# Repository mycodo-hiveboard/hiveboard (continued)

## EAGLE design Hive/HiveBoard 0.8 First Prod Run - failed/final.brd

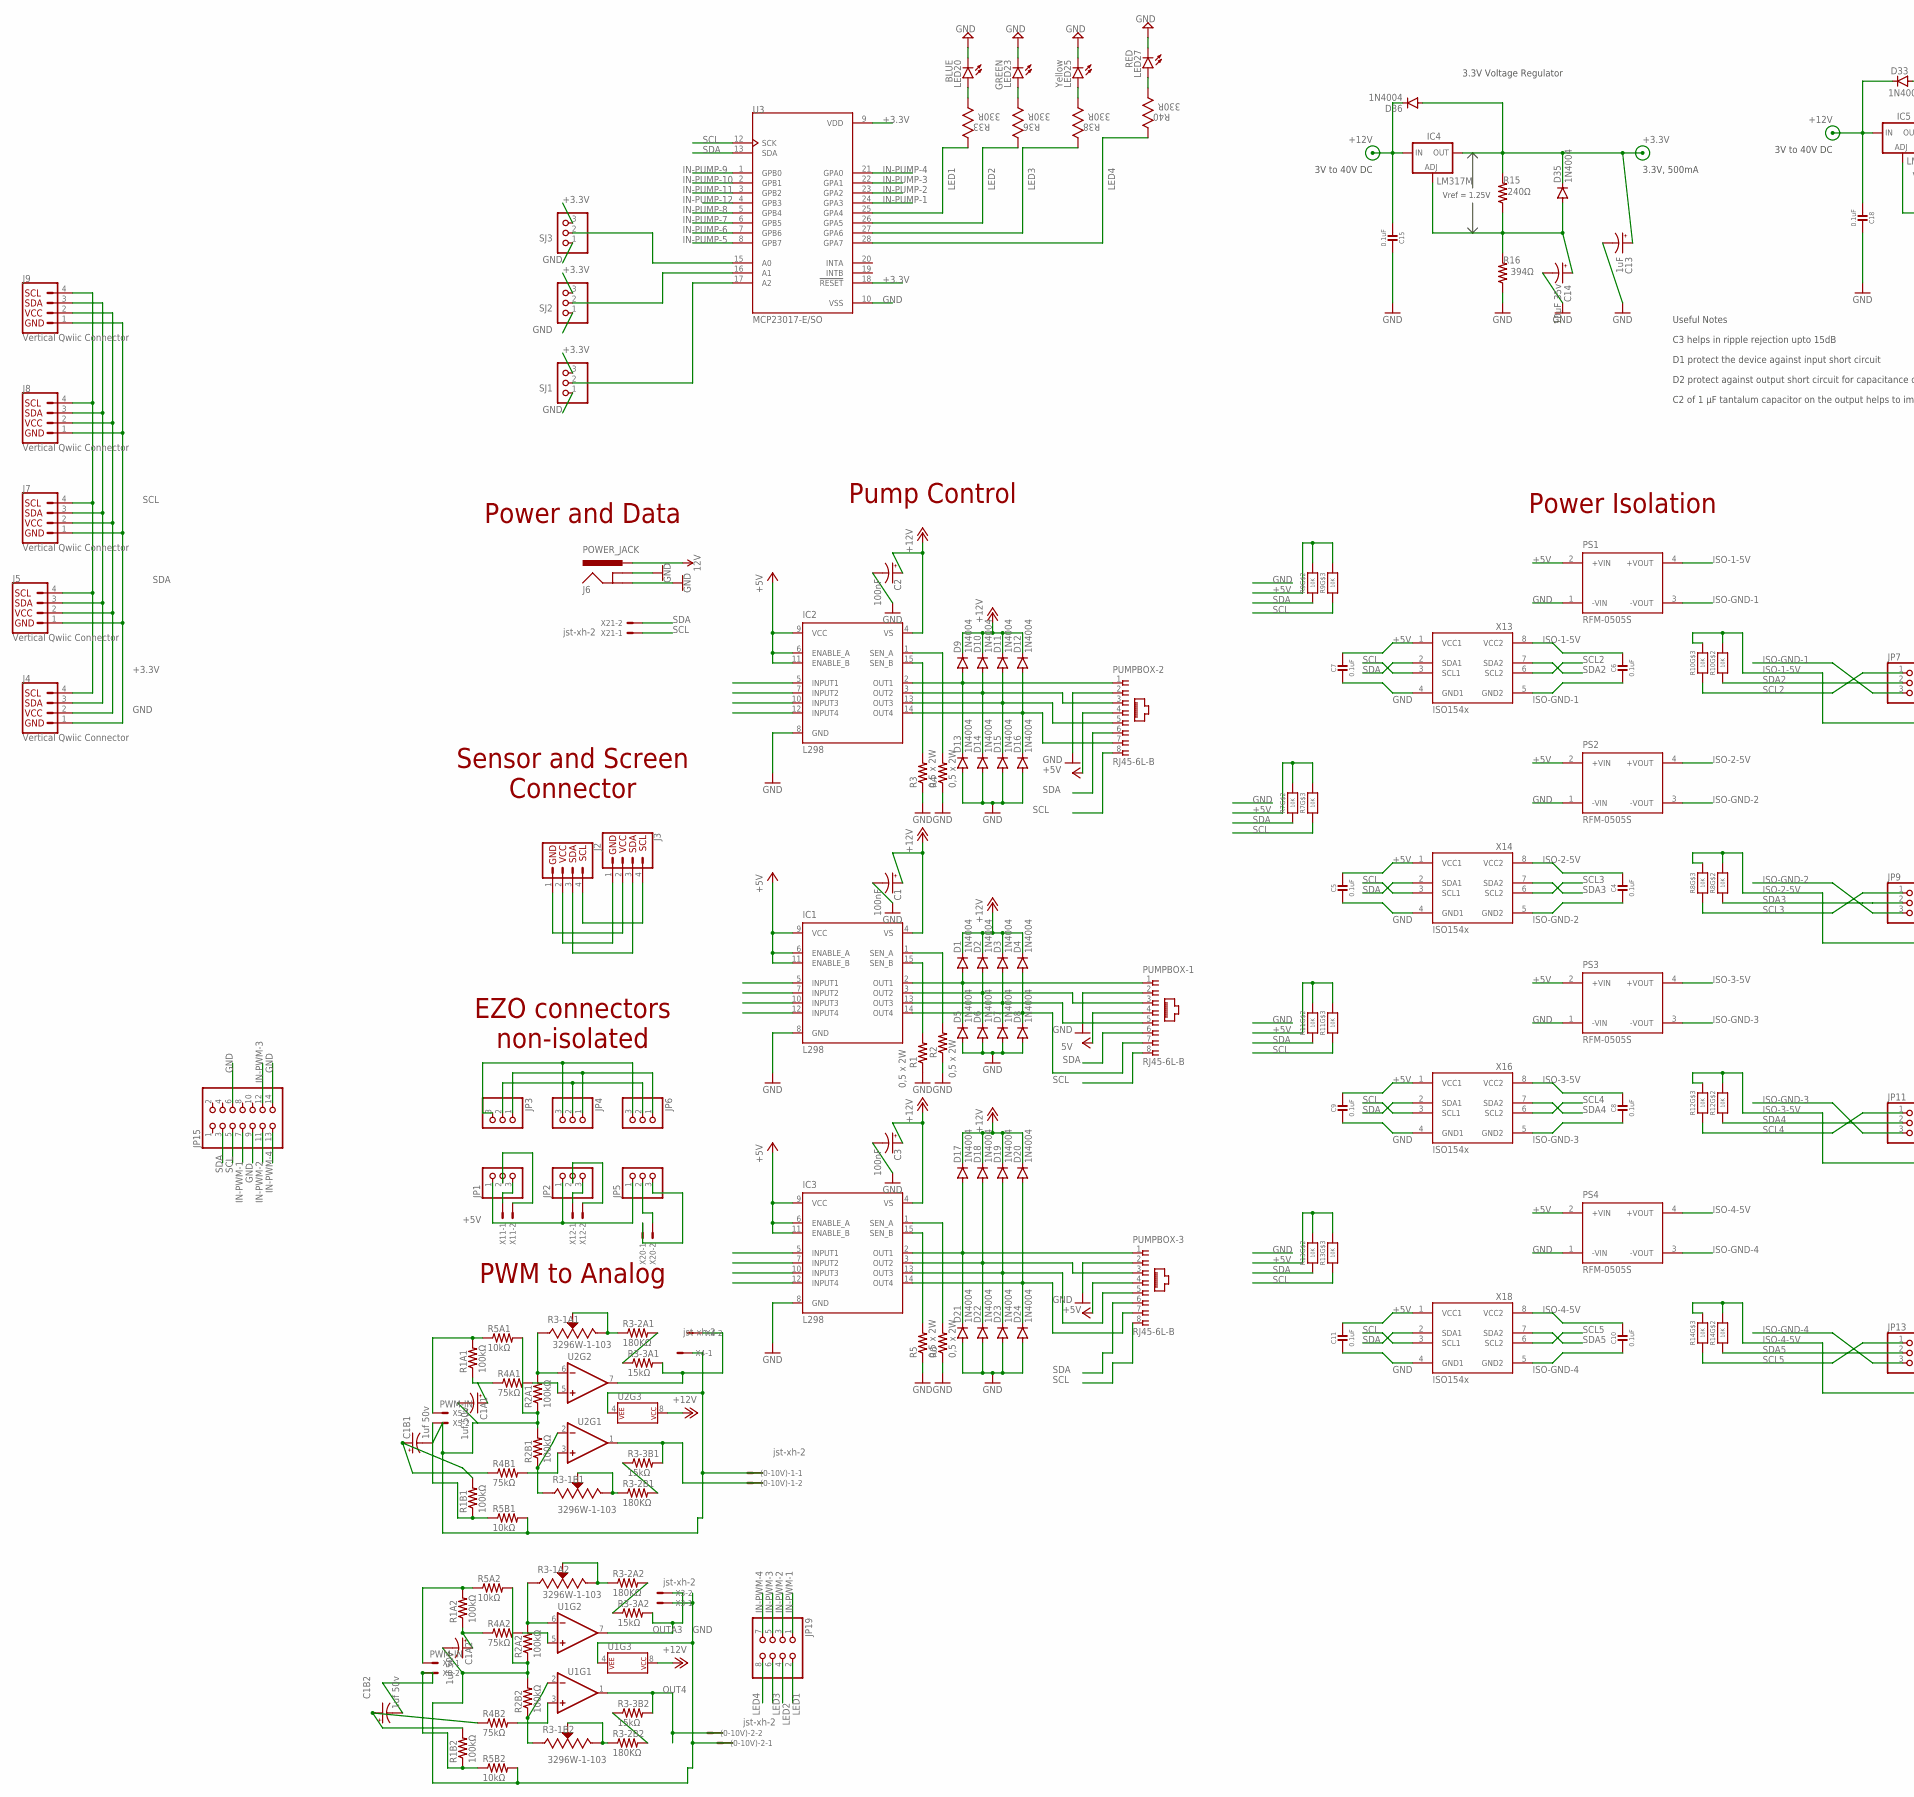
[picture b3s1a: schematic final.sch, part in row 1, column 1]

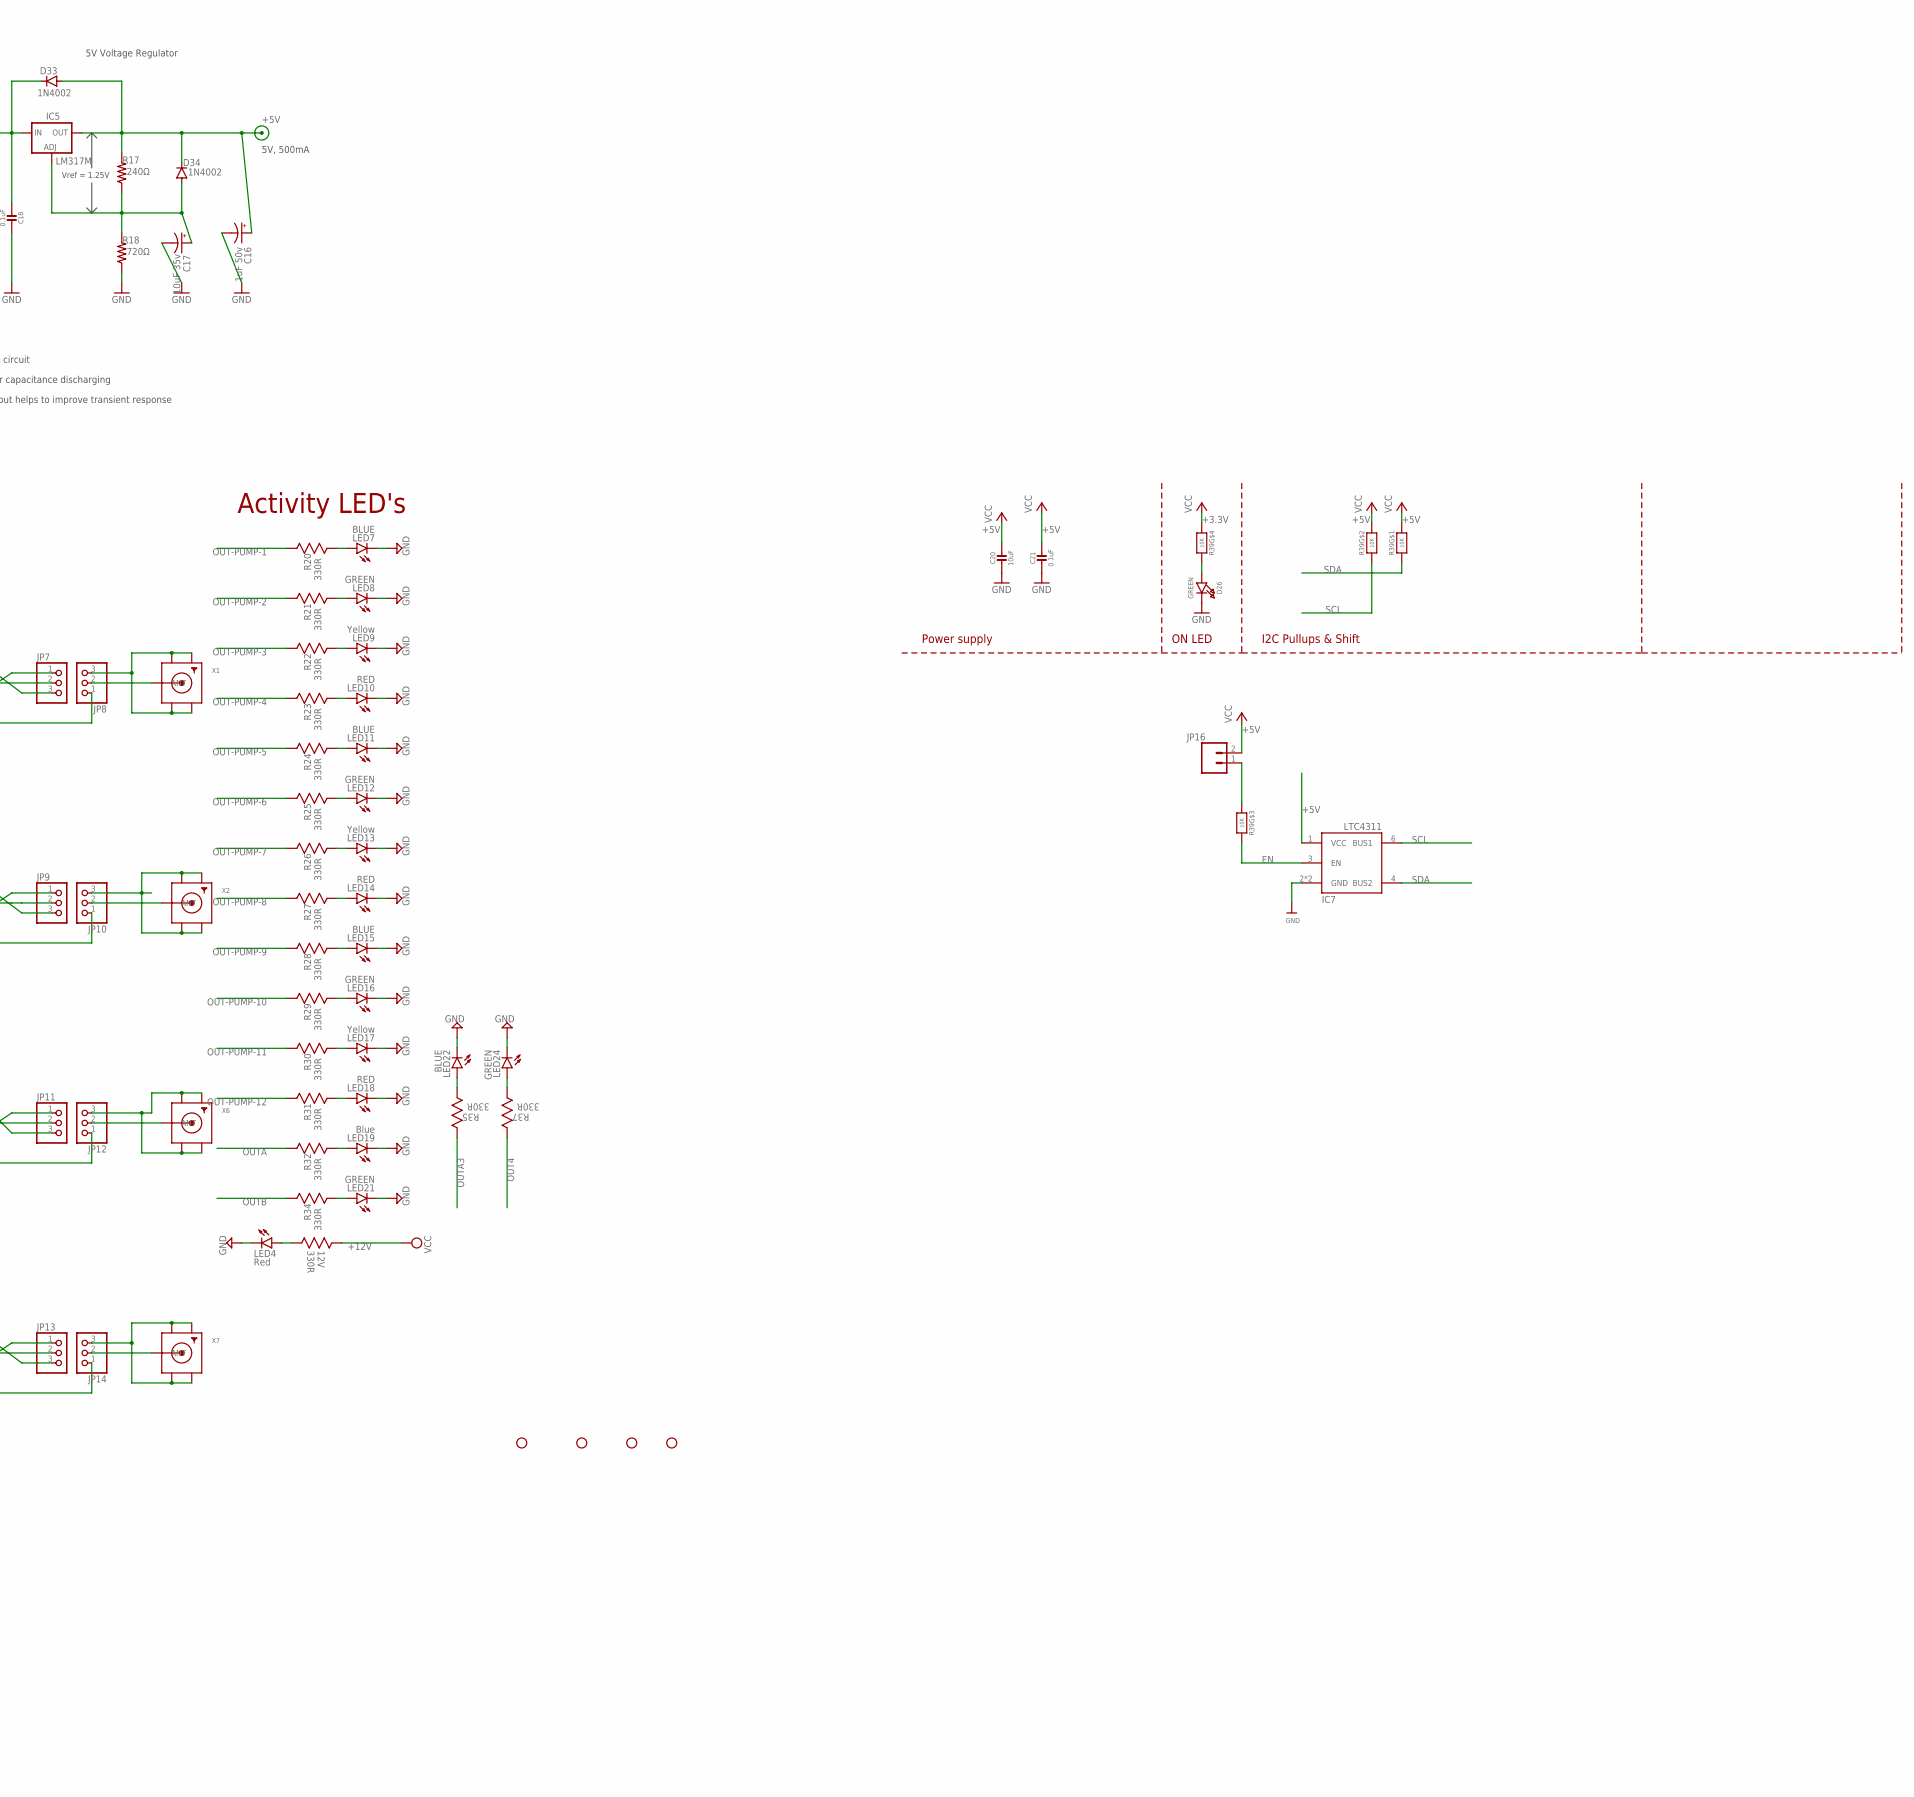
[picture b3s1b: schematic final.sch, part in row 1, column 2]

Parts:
12V: 330R; RESC1608X60N
(0-10V)-1, (0-10V)-2: jst-xh-2; JST-XH-02-PACKAGE-LONG-PAD
C1, C2, C3: 100nF; UD-4X5,8_NICHICON
C1A1, C1A2, C1B1, C1B2: 1uf 50v; UD-4X5,8_NICHICON
C4, C5, C6, C7, C8, C9, C10, C11, C15, C18, C21: 0.1uF; 0603-NO
C13: 1uF; UD-4X5,8_NICHICON
C14, C17: 10uF 35v; UD-4X5,8_NICHICON
C16: 1uF 50v; UD-4X5,8_NICHICON
C20: 10uF; 0805-NO
D1, D2, D3, D4, D5, D6, D7, D8, D9, D10, D11, D12, D13, D14, D15, D16, D17, D18, D19, D20, D21, D22, D23, D24, D35, D36: 1N4004; DO214BA
D26: GREEN; CHIPLED_0603_NOOUTLINE
D33, D34: 1N4002; DO214BA
H5, H6, H7, H8: STAND-OFF
IC1, IC2, IC3: L298; MULTIWATT-15
IC4, IC5: LM317MBSTT3; SOT223; PARTNUMBER LM317M
IC7: LTC4311_SC70; SC70-6L
J2, J3: I2C_STANDARD; 1X04
J4, J5, J7, J8, J9: Vertical Qwiic Connector; JST04_1MM_VERT
J6: POWER_JACK; POWER_JACK_PTH
JP1, JP2, JP3, JP4, JP5, JP6, JP7, JP8, JP9, JP10, JP11, JP12, JP13, JP14: PINHD-1X3CB; 1X03-CLEANBIG
JP15: PINHD-2X7; 2X07
JP16: CONN_02; 1X02
JP19: PINHD-2X4; 2X04
LED4: Red; LED-0603
LED7, LED11, LED15, LED20, LED22: BLUE; LED-0603
LED8, LED12, LED16, LED21, LED23, LED24: GREEN; LED-0603
LED9, LED13, LED17, LED25: Yellow; LED-0603
LED10, LED14, LED18, LED27: RED; LED-0603
LED19: Blue; LED-0603
PS1, PS2, PS3, PS4: RFM-0505S; CONV_RFM-0505S
PUMPBOX-1, PUMPBOX-2, PUMPBOX-3: RJ45-6L-B; RJ45-NO-SHIELD
R1, R2, R3, R4, R5, R6: 0,5 x 2W; R2512
R1A1, R1A2, R1B1, R1B2, R2A1, R2A2, R2B1, R2B2: 100kΩ; M1206
R3-1A1, R3-1A2, R3-1B1, R3-1B2: 3296W-1-103; TRIM_3296W-1-103
R3-2A1, R3-2A2, R3-2B1, R3-2B2: 180KΩ; M1206
R3-3A1, R3-3A2, R3-3B1, R3-3B2: 15kΩ; M1206
R4A1, R4A2, R4B1, R4B2: 75kΩ; M1206
R5A1, R5A2, R5B1, R5B2: 10kΩ; M1206
R7, R8, R9, R10, R11, R12, R13, R14, R39: 10K; RESPACK_4X0603
R15, R17: 240Ω; M0805
R16: 394Ω; M0805
R18: 720Ω; M0805
R20, R21, R22, R23, R24, R25, R26, R27, R28, R29, R30, R31, R32, R33, R34, R35, R36, R37, R38, R40: 330R; RESC1608X60N
SJ1, SJ2, SJ3: PINHD-1X3; 1X03
U1, U2: LM358; SO08
U3: MCP23017-E/SO; SOIC127P1030X265-28N
X1, X2, X6, X7: SMACONNECTOR_EDGE; SMA_EDGELAUNCH
X3, X4, X11, X12, X20, X21: jst-xh-2; JST-XH-02-PACKAGE-LONG-PAD
X5, X8: PWM-IN; JST-XH-02-PACKAGE-LONG-PAD
X13, X14, X16, X18: ISO154X; SOIC8_150MIL

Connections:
12V: J6.PWR
+3.3V: C13.+, D35.C, D36.A, IC4.4 (OUT), J4.2, J5.2, J7.2, J8.2, J9.2, R15.2, R39.4 (1), SJ1.3, SJ2.3, SJ3.3, U3.9 (VDD), U3.18 (!RESET)
+5V: C5.1, C7.1, C9.1, C11.1, C16.+, C20.1, C21.1, D33.A, D34.C, IC1.6 (ENABLE_A), IC1.9 (VCC), IC1.11 (ENABLE_B), IC2.6 (ENABLE_A), IC2.9 (VCC), IC2.11 (ENABLE_B), IC3.6 (ENABLE_A), IC3.9 (VCC), IC3.11 (ENABLE_B), IC5.4 (OUT), IC7.1 (VCC), J2.1, J3.2, JP1.1, JP2.1, JP5.1, JP16.2, PS1.2 (+VIN), PS2.2 (+VIN), PS3.2 (+VIN), PS4.2 (+VIN), PUMPBOX-1.4, PUMPBOX-2.4, PUMPBOX-3.4, R7.6 (2), R7.7 (2), R9.6 (2), R9.7 (2), R11.6 (2), R11.7 (2), R13.6 (2), R13.7 (2), R17.2, R39.7 (2), R39.8 (2), X13.1 (VCC1), X14.1 (VCC1), X16.1 (VCC1), X18.1 (VCC1)
+12V: 12V.1 (R1), C1.+, C2.+, C3.+, C15.2, C18.2, D1.C, D2.C, D3.C, D4.C, D9.C, D10.C, D11.C, D12.C, D17.C, D18.C, D19.C, D20.C, D33.C, D36.C, IC1.4 (VS), IC2.4 (VS), IC3.4 (VS), IC4.3 (IN), IC5.3 (IN), U1.8 (P$V+), U2.8 (P$V+)
EN: IC7.3 (EN), R39.6 (2)
GND: (0-10V)-1.1, (0-10V)-2.1, C1.-, C1A1.-, C1A2.-, C1B1.-, C2.-, C3.-, C5.2, C7.2, C9.2, C11.2, C13.-, C14.-, C15.1, C16.-, C17.-, C18.1, C20.2, C21.2, D5.A, D6.A, D7.A, D8.A, D13.A, D14.A, D15.A, D16.A, D21.A, D22.A, D23.A, D24.A, D26.C, IC1.8 (GND), IC2.8 (GND), IC3.8 (GND), IC7.2 (GND), IC7.5 (GND), J2.2, J3.1, J4.1, J5.1, J6.GND, J6.GNDBREAK, J7.1, J8.1, J9.1, JP3.3, JP4.3, JP6.3, JP15.6, JP15.9, JP15.14, LED4.C, LED7.C, LED8.C, LED9.C, LED10.C, LED11.C, LED12.C, LED13.C, LED14.C, LED15.C, LED16.C, LED17.C, LED18.C, LED19.C, LED20.C, LED21.C, LED22.C, LED23.C, LED24.C, LED25.C, LED27.C, PS1.1 (-VIN), PS2.1 (-VIN), PS3.1 (-VIN), PS4.1 (-VIN), PUMPBOX-1.2, PUMPBOX-2.2, PUMPBOX-3.2, R1.1, R2.1, R2A1.1, R2A2.1, R2B1.2, R2B2.2, R3.1, R4.1, R5.1, R5A1.2, R5A2.2, R5B1.2, R5B2.2, R6.1, R16.1, R18.1, SJ1.1, SJ2.1, SJ3.1, U1.4 (P$V-), U2.4 (P$V-), U3.10 (VSS), X3.1, X4.1, X13.4 (GND1), X14.4 (GND1), X16.4 (GND1), X18.4 (GND1)
IN-PUMP-1: IC1.5 (INPUT1), U3.24 (GPA3)
IN-PUMP-2: IC1.7 (INPUT2), U3.23 (GPA2)
IN-PUMP-3: IC1.10 (INPUT3), U3.22 (GPA1)
IN-PUMP-4: IC1.12 (INPUT4), U3.21 (GPA0)
IN-PUMP-5: IC2.5 (INPUT1), U3.8 (GPB7)
IN-PUMP-6: IC2.7 (INPUT2), U3.7 (GPB6)
IN-PUMP-7: IC2.10 (INPUT3), U3.6 (GPB5)
IN-PUMP-8: IC2.12 (INPUT4), U3.5 (GPB4)
IN-PUMP-9: IC3.5 (INPUT1), U3.1 (GPB0)
IN-PUMP-10: IC3.7 (INPUT2), U3.2 (GPB1)
IN-PUMP-11: IC3.10 (INPUT3), U3.3 (GPB2)
IN-PUMP-12: IC3.12 (INPUT4), U3.4 (GPB3)
IN-PWM-1: JP15.7, JP19.1, R1A1.2, R5A1.1, X5.1
IN-PWM-2: JP15.11, JP19.3, R1B1.1, R5B1.1, X5.2
IN-PWM-3: JP15.12, JP19.5, R1A2.2, R5A2.1, X8.1
IN-PWM-4: C1B2.-, JP15.13, JP19.7, R1B2.1, R5B2.1, X8.2
ISO-1-5V: C6.1, JP8.1, PS1.4 (+VOUT), R10.6 (2), R10.7 (2), X13.8 (VCC2)
ISO-2-5V: C4.1, JP10.1, PS2.4 (+VOUT), R8.6 (2), R8.7 (2), X14.8 (VCC2)
ISO-3-5V: C8.1, JP12.1, PS3.4 (+VOUT), R12.6 (2), R12.7 (2), X16.8 (VCC2)
ISO-4-5V: C10.1, JP14.1, PS4.4 (+VOUT), R14.6 (2), R14.7 (2), X18.8 (VCC2)
ISO-GND-1: C6.2, JP7.3, PS1.3 (-VOUT), X13.5 (GND2)
ISO-GND-2: C4.2, JP9.3, PS2.3 (-VOUT), X14.5 (GND2)
ISO-GND-3: C8.2, JP11.3, PS3.3 (-VOUT), X16.5 (GND2)
ISO-GND-4: C10.2, JP13.3, PS4.3 (-VOUT), X18.5 (GND2)
LED1: JP19.2, R33.1 (R1), U3.25 (GPA4)
LED2: JP19.4, R36.1 (R1), U3.26 (GPA5)
LED3: JP19.6, R38.1 (R1), U3.27 (GPA6)
LED4: JP19.8, R40.1 (R1), U3.28 (GPA7)
unnamed: IC2.1 (SEN_A), R4.2
unnamed: IC2.15 (SEN_B), R3.2
unnamed: IC3.1 (SEN_A), R6.2
unnamed: IC3.15 (SEN_B), R5.2
unnamed: C14.+, D35.A, IC4.1 (ADJ), R15.1, R16.2
unnamed: R3-1B2.2 (WIPER), R3-1B2.3 (CW), R3-2B2.1
unnamed: LED20.A, R33.2 (R2)
unnamed: R3-2B2.2, R3-3B2.1
unnamed: IC1.1 (SEN_A), R2.2
unnamed: IC1.15 (SEN_B), R1.2
unnamed: C17.+, D34.A, IC5.1 (ADJ), R17.1, R18.2
unnamed: JP12.3, X6.GND@1 (GND4), X6.GND@2 (GND3), X6.GND@3 (GND2), X6.GND@4 (GND1)
unnamed: LED23.A, R36.2 (R2)
unnamed: JP8.3, X1.GND@1 (GND4), X1.GND@2 (GND3), X1.GND@3 (GND2), X1.GND@4 (GND1)
unnamed: JP10.3, X2.GND@1 (GND4), X2.GND@2 (GND3), X2.GND@3 (GND2), X2.GND@4 (GND1)
unnamed: JP8.2, X1.P (ANT)
unnamed: R3-1B1.2 (WIPER), R3-1B1.3 (CW), R3-2B1.1
unnamed: R3-2B1.2, R3-3B1.1
unnamed: R3-1A1.2 (WIPER), R3-1A1.3 (CW), R3-2A1.1
unnamed: R3-2A1.2, R3-3A1.1
unnamed: C1A1.+, R1A1.1, R4A1.1
unnamed: C1B1.+, R1B1.2, R4B1.1
unnamed: R2A1.2, R3-1A1.1 (CCW), U2.6 (-IN)
unnamed: R2B1.1, R3-1B1.1 (CCW), U2.2 (-IN)
unnamed: R4A1.2, U2.5 (+IN)
unnamed: R4B1.2, U2.3 (+IN)
unnamed: C1B2.+, R1B2.2, R4B2.1
unnamed: LED22.A, R35.2 (R2)
unnamed: LED24.A, R37.2 (R2)
unnamed: JP14.3, X7.GND@1 (GND4), X7.GND@2 (GND3), X7.GND@3 (GND2), X7.GND@4 (GND1)
unnamed: JP5.2, X20.2
unnamed: JP10.2, X2.P (ANT)
unnamed: JP5.3, X20.1
unnamed: JP2.3, X12.1
unnamed: JP2.2, X12.2
unnamed: JP12.2, X6.P (ANT)
unnamed: JP1.3, X11.1
unnamed: JP1.2, X11.2
unnamed: JP14.2, X7.P (ANT)
unnamed: D26.A, R39.5 (2)
unnamed: JP16.1, R39.3 (1)
unnamed: 12V.2 (R2), LED4.A
unnamed: LED7.A, R20.2 (R2)
unnamed: LED8.A, R21.2 (R2)
unnamed: LED9.A, R22.2 (R2)
unnamed: LED10.A, R23.2 (R2)
unnamed: LED11.A, R24.2 (R2)
unnamed: LED12.A, R25.2 (R2)
unnamed: LED13.A, R26.2 (R2)
unnamed: LED14.A, R27.2 (R2)
unnamed: LED15.A, R28.2 (R2)
unnamed: LED16.A, R29.2 (R2)
unnamed: LED17.A, R30.2 (R2)
unnamed: LED18.A, R31.2 (R2)
unnamed: LED19.A, R32.2 (R2)
unnamed: R3-1A2.2 (WIPER), R3-1A2.3 (CW), R3-2A2.1
unnamed: LED21.A, R34.2 (R2)
unnamed: LED25.A, R38.2 (R2)
unnamed: R3-2A2.2, R3-3A2.1
unnamed: LED27.A, R40.2 (R2)
unnamed: C1A2.+, R1A2.1, R4A2.1
unnamed: R2A2.2, R3-1A2.1 (CCW), U1.6 (-IN)
unnamed: R2B2.1, R3-1B2.1 (CCW), U1.2 (-IN)
unnamed: R4A2.2, U1.5 (+IN)
unnamed: R4B2.2, U1.3 (+IN)
unnamed: SJ3.2, U3.15 (A0)
unnamed: SJ2.2, U3.16 (A1)
unnamed: SJ1.2, U3.17 (A2)
OUT4: (0-10V)-2.2, R3-3B2.2, R37.1 (R1), U1.1 (OUT)
OUT-PUMP-1: D1.A, D5.C, IC1.2 (OUT1), PUMPBOX-1.1, R20.1 (R1)
OUT-PUMP-2: D2.A, D6.C, IC1.3 (OUT2), PUMPBOX-1.3, R21.1 (R1)
OUT-PUMP-3: D3.A, D7.C, IC1.13 (OUT3), PUMPBOX-1.5, R22.1 (R1)
OUT-PUMP-4: D4.A, D8.C, IC1.14 (OUT4), PUMPBOX-1.7, R23.1 (R1)
OUT-PUMP-5: D9.A, D13.C, IC2.2 (OUT1), PUMPBOX-2.1, R24.1 (R1)
OUT-PUMP-6: D10.A, D14.C, IC2.3 (OUT2), PUMPBOX-2.3, R25.1 (R1)
OUT-PUMP-7: D11.A, D15.C, IC2.13 (OUT3), PUMPBOX-2.5, R26.1 (R1)
OUT-PUMP-8: D12.A, D16.C, IC2.14 (OUT4), PUMPBOX-2.7, R27.1 (R1)
OUT-PUMP-9: D17.A, D21.C, IC3.2 (OUT1), PUMPBOX-3.1, R28.1 (R1)
OUT-PUMP-10: D18.A, D22.C, IC3.3 (OUT2), PUMPBOX-3.3, R29.1 (R1)
OUT-PUMP-11: D19.A, D23.C, IC3.13 (OUT3), PUMPBOX-3.5, R30.1 (R1)
OUT-PUMP-12: D20.A, D24.C, IC3.14 (OUT4), PUMPBOX-3.7, R31.1 (R1)
OUTA: R3-3A1.2, R32.1 (R1), U2.7 (OUT), X4.2
OUTA3: R3-3A2.2, R35.1 (R1), U1.7 (OUT), X3.2
OUTB: (0-10V)-1.2, R3-3B1.2, R34.1 (R1), U2.1 (OUT)
SCL: IC7.6 (BUS1), J2.3, J3.3, J4.4, J5.4, J7.4, J8.4, J9.4, JP3.1, JP4.1, JP6.1, JP15.5, PUMPBOX-1.8, PUMPBOX-2.8, PUMPBOX-3.8, R7.3 (1), R9.3 (1), R11.3 (1), R13.3 (1), R39.2 (1), U3.12 (SCK), X13.3 (SCL1), X14.3 (SCL1), X16.3 (SCL1), X18.3 (SCL1), X21.1
SCL2: JP7.1, R10.3 (1), X13.6 (SCL2)
SCL3: JP9.1, R8.3 (1), X14.6 (SCL2)
SCL4: JP11.1, R12.3 (1), X16.6 (SCL2)
SCL5: JP13.1, R14.3 (1), X18.6 (SCL2)
SDA: IC7.4 (BUS2), J2.4, J3.4, J4.3, J5.3, J7.3, J8.3, J9.3, JP3.2, JP4.2, JP6.2, JP15.3, PUMPBOX-1.6, PUMPBOX-2.6, PUMPBOX-3.6, R7.2 (1), R9.2 (1), R11.2 (1), R13.2 (1), R39.1, U3.13 (SDA), X13.2 (SDA1), X14.2 (SDA1), X16.2 (SDA1), X18.2 (SDA1), X21.2
SDA2: JP7.2, R10.2 (1), X13.7 (SDA2)
SDA3: JP9.2, R8.2 (1), X14.7 (SDA2)
SDA4: JP11.2, R12.2 (1), X16.7 (SDA2)
SDA5: JP13.2, R14.2 (1), X18.7 (SDA2)

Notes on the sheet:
Power Isolation
Pump Control
PWM to Analog
EZO connectors non-isolated
Sensor and Screen Connector
Power and Data
3.3V Voltage Regulator
C3 helps in ripple rejection upto 15dB
D1 protect the device against input short circuit
D2 protect against output short circuit for capacitance discharging
C2 of 1 µF tantalum capacitor on the output helps to improve transient response
Useful Notes
3V to 40V DC
Vref = 1.25V
3.3V, 500mA
5V Voltage Regulator
5V, 500mA
Activity LED's
I2C Pullups & Shift
ON LED
Power supply

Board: 4 copper layers, 209 parts (0 on the bottom side), 127 nets, no tracks yet.

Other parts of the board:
U$1, U$2: STAND-OFF

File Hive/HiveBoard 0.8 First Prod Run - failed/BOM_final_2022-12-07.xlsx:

No. | Quantity | Comment | Designator | Footprint | Value | Manufacturer Part | Manufacturer | Supplier Part | Supplier
1 | 21 | 330R | 12V,R20,R21,R22,R23,R24,R25,R26,R27,R28,R29,R30,R31,R32,R33,R34,R35,R36,R37,R38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 | RESC1608X60N
2 | 8 | jst-xh-2 | (0-10V)-1,(0-10V)-2,X3,X4,X11,X12,X20,X21 | JST-XH-02-PACKAGE-LONG-PAD
3 | 3 | 100nF | C1,C2,C3 | UD-4X5,8_NICHICON |  | C271438
4 | 4 | 1uf 50v | C1A1,C1A2,C1B1,C1B2 | UD-4X5,8_NICHICON |  | C3348
5 | 11 | 0.1uF | C4,C5,C6,C7,C8,C9,C10,C11,C15,C18,C21 | 0603-NO
6 | 1 | 1uF | C13 | UD-4X5,8_NICHICON |  | C3348
7 | 2 | 10uF 35v | C14,C17 | UD-4X5,8_NICHICON |  | C72485
8 | 1 | 1uF 50v | C16 | UD-4X5,8_NICHICON |  | C3348
9 | 1 | 10uF | C20 | 0805-NO
10 | 26 | 1N4004 | D1,D2,D3,D4,D5,D6,D7,D8,D9,D10,D11,D12,D13,D14,D15,D16,D17,D18,D19,D20,D21,D22,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 | DO214BA
11 | 1 | GREEN | D26 | CHIPLED_0603_NOOUTLINE
12 | 2 | 1N4002 | D33,D34 | DO214BA |  | C727082
13 | 4 | STAND-OFF | H5,H6,H7,H8 | STAND-OFF
14 | 3 | L298 | IC1,IC2,IC3 | MULTIWATT-15
15 | 2 | LM317MBSTT3 | IC4,IC5 | SOT223
16 | 1 | LTC4311_SC70 | IC7 | SC70-6L |  | C580856
17 | 1 | DCJ0202 | J1 | DCJ0202
18 | 2 |  | J2,J3 | 1X04 |  | C124378
19 | 5 | Vertical Qwiic Connector | J4,J5,J7,J8,J9 | JST04_1MM_VERT |  | C2859067
20 | 14 |  | JP1,JP2,JP3,JP4,JP5,JP6,JP7,JP8,JP9,JP10,JP11,JP12,JP13,JP14 | 1X03-CLEANBIG |  | C2886705
21 | 1 |  | JP15 | 2X07 |  | C71397
22 | 1 |  | JP16 | 1X02 |  | C492401
23 | 1 |  | JP19 | 2X04 |  | C124386
24 | 1 | Red | LED4 | LED-0603 |  | C84263
25 | 5 | BLUE | LED7,LED11,LED15,LED20,LED22 | LED-0603
26 | 6 | GREEN | LED8,LED12,LED16,LED21,LED23,LED24 | LED-0603 |  | C72043
27 | 4 | Yellow | LED9,LED13,LED17,LED25 | LED-0603 |  | C389521
28 | 4 | RED | LED10,LED14,LED18,LED27 | LED-0603 |  | C84263
29 | 1 | Blue | LED19 | LED-0603 |  | C72041
30 | 4 | RFM-0505S | PS1,PS2,PS3,PS4 | CONV_RFM-0505S
31 | 3 | RJ45-6L-B | PUMPBOX-1,PUMPBOX-2,PUMPBOX-3 | RJ45-NO-SHIELD |  | C86577
32 | 6 | 0,5 x 2W | R1,R2,R3,R4,R5,R6 | R2512 |  | C469426
33 | 8 | 100kΩ | R1A1,R1A2,R1B1,R1B2,R2A1,R2A2,R2B1,R2B2 | M1206
34 | 4 | 3296W-1-103 | R3-1A1,R3-1A2,R3-1B1,R3-1B2 | TRIM_3296W-1-103
35 | 4 | 180KΩ | R3-2A1,R3-2A2,R3-2B1,R3-2B2 | M1206
36 | 4 | 15kΩ | R3-3A1,R3-3A2,R3-3B1,R3-3B2 | M1206
37 | 4 | 75kΩ | R4A1,R4A2,R4B1,R4B2 | M1206
38 | 4 | 10kΩ | R5A1,R5A2,R5B1,R5B2 | M1206
39 | 9 | 10K | R7,R8,R9,R10,R11,R12,R13,R14,R39 | RESPACK_4X0603 |  | C29718
40 | 2 | 240Ω | R15,R17 | M0805
41 | 1 | 394Ω | R16 | M0805
42 | 1 | 720Ω | R18 | M0805
43 | 3 |  | SJ1,SJ2,SJ3 | 1X03 |  | C49257
44 | 2 | LM358 | U1,U2 | SO08
45 | 1 | MCP23017-E/SO | U3 | SOIC127P1030X265-28N
46 | 2 |  | U$1,U$2 | STAND-OFF
47 | 4 |  | X1,X2,X6,X7 | SMA_EDGELAUNCH |  | C1509219
48 | 2 | PWM-IN | X5,X8 | JST-XH-02-PACKAGE-LONG-PAD
49 | 4 | ISO154X | X13,X14,X16,X18 | SOIC8_150MIL

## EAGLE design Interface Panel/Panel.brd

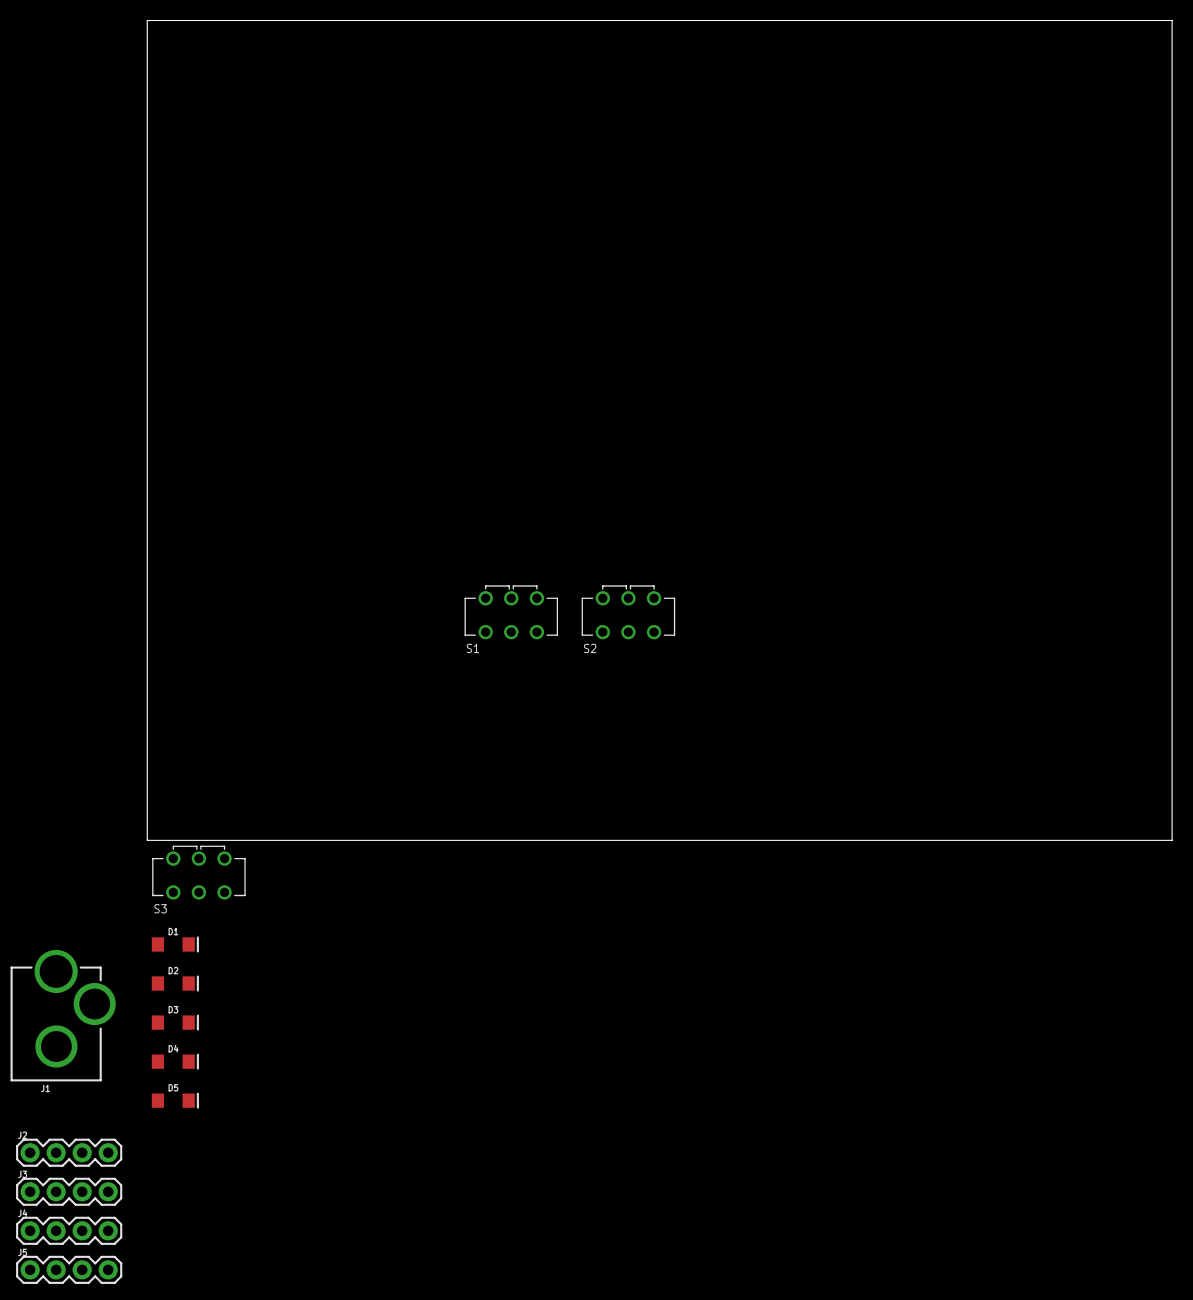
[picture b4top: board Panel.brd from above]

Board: 2 copper layers, 100.0 x 80.0 mm, 13 parts (0 on the bottom side), 2 nets, no tracks yet.

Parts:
D1: BLUE; LED-1206
D2: GREEN; LED-1206
D3, D4: RED; LED-1206
D5: Yellow; LED-1206
J1: POWER_JACKPTH_LOCK; POWER_JACK_PTH_LOCK
J2, J3, J4, J5: 1X04
S1, S2, S3: JS202011CQN

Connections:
1: J2.1, J3.1, J4.1, J5.1
2: J2.2, J3.2, J4.2, J5.2
